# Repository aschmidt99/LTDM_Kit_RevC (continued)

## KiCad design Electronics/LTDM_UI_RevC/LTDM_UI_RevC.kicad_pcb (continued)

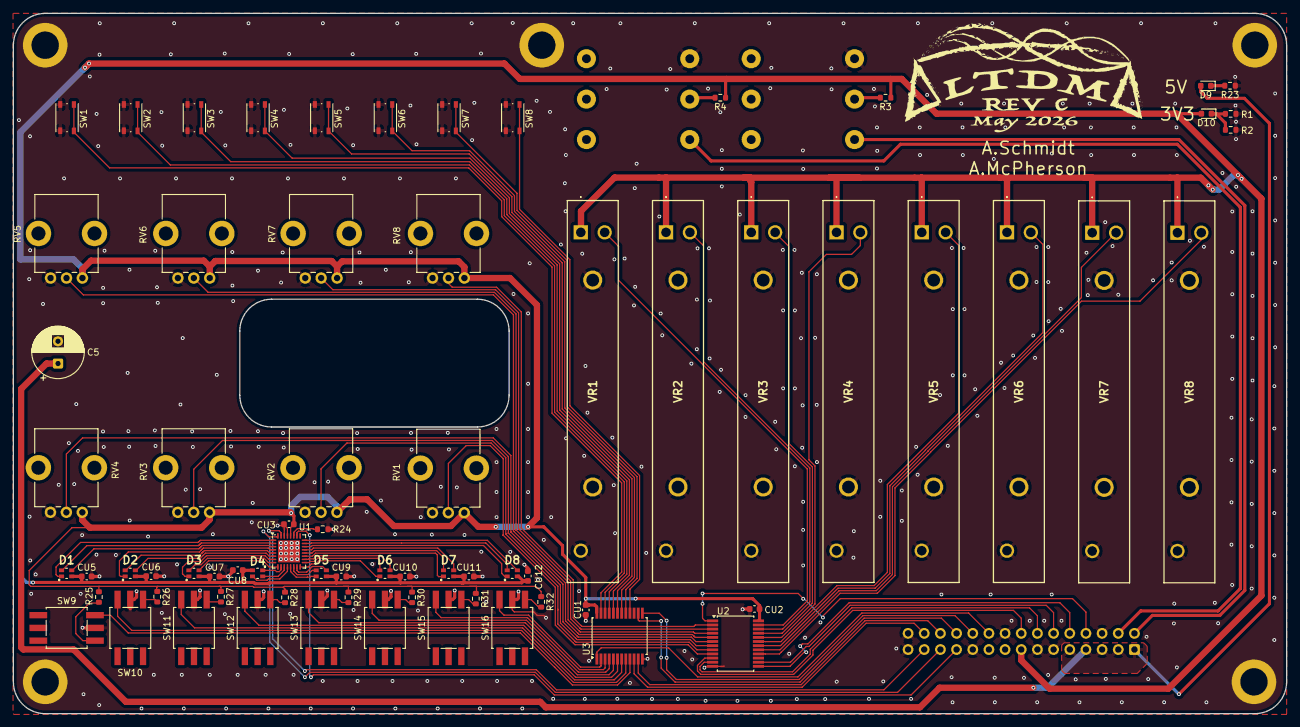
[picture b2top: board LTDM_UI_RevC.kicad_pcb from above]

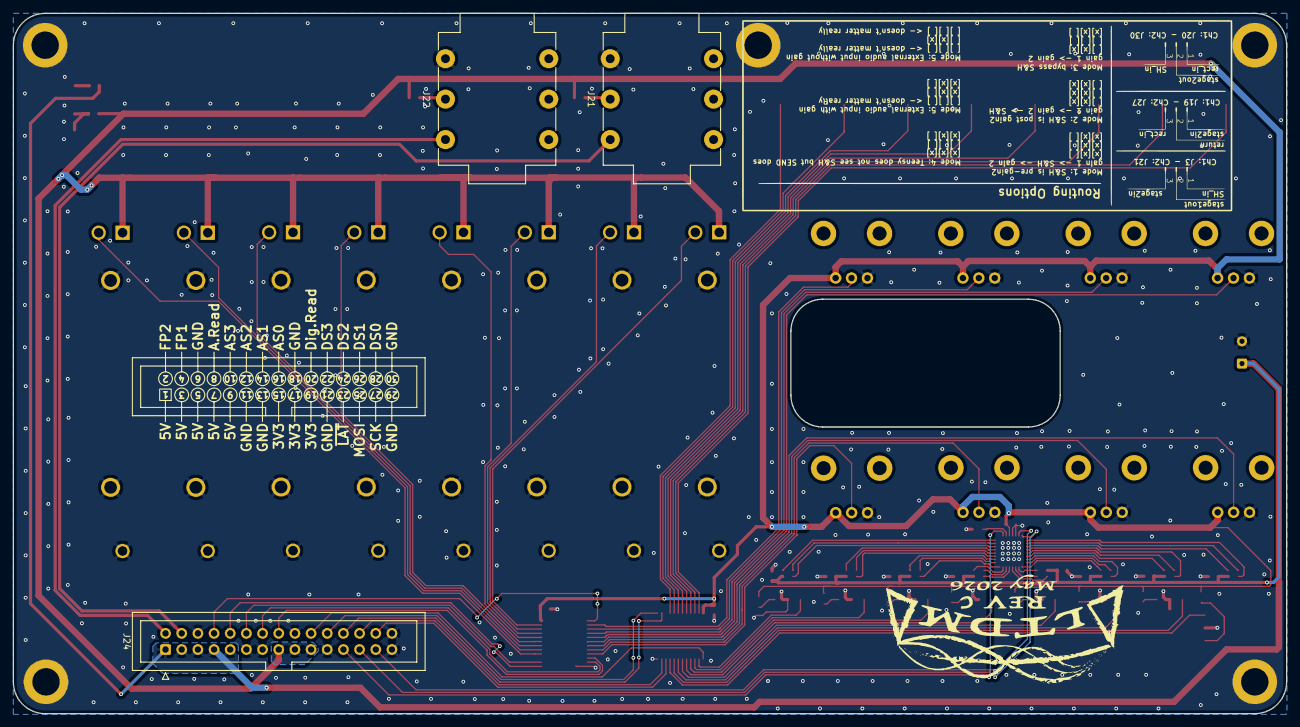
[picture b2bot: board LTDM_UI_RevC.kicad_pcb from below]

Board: 2 copper layers, 200.0 x 110.0 mm, 80 parts (4 on the bottom side), 87 nets.

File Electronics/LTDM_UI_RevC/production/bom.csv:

Designator,Footprint,Quantity,Value,LCSC Part #
C5,CP_Radial_D8.0mm_P3.50mm,1,220u,C45072
"CU1, CU10, CU11, CU12, CU2, CU3, CU5, CU6, CU7, CU8, CU9",0603,11,100n,
"D1, D2, D3, D4, D5, D6, D7, D8",19237R6GHBHCA012T,8,LED_RGBA,C60105
"D10, D9",0603,2,LED,C79636
"J21, J22",Jack_6.35mm_Neutrik_NMJ6HCD2_Horizontal,2,NMJ6HCD2,C368502
J24,IDC-Header_2x15_P2.54mm_Vertical,1,Conn_02x15_Odd_Even,C358748
"R1, R2, R23",0603,3,120,
R24,0603,1,2.2k,
"R25, R26, R27, R28, R29, R30, R31, R32",0603,8,10k,
"R3, R4",0603,2,100,
"RV1, RV2",Potentiometer_Bourns_PTV09A-1_Single_Vertical,2,10k, C5357831
"RV3, RV4, RV5, RV6, RV7, RV8",Potentiometer_Bourns_PTV09A-1_Single_Vertical,6,10k,C5357831
"SW1, SW2, SW3, SW4, SW5, SW6, SW7, SW8",SW_Push_1P1T_NO_Vertical_Wuerth_434133025816,8,tactile,C5504987
"SW10, SW11, SW12, SW13, SW14, SW15, SW16, SW9",SW_Push_DPDT_PS-5850SVB-6PL,8,SW_Push_DPDT,C5155567
U1,QFN-32-1EP_5x5mm_P0.5mm_EP3.45x3.45mm,1,TLC5947RHB,C181402
"U2, U3",SSOP-24_5.3x8.2mm_P0.65mm,2,CD74HC4067SM,C98457
"VR1, VR2, VR3, VR4, VR5, VR6, VR7, VR8",RS45111A900F,8,RS45111A900F,C470640

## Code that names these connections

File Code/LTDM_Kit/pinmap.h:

// pinmap.h
#ifndef PINMAP_H
#define PINMAP_H

// OUTPUTS //
// FLEX PWM definitions
constexpr int SENSE_ALT     = 4; // FlexPWM 2.0A - alternate sense pulse (in case of small timing adjustments for S&H)
constexpr int SENSE_PULSE   = 5; // FlexPWM 2.1A - primary sense pulse (triggers ISR, traditionally triggers S&H)
constexpr int CH1_PACTUATE  = 6; // FlexPWM 2.2A (Val2+3) - Channel 1 Actuate PMOS Positive Pulse
constexpr int CH1_NACTUATE  = 9; // FlexPWM 2.2B (Val4+5) - Channel 1 Actuate NMOS Negative Pulse
constexpr int CH2_PACTUATE  = 36; //FlexPWM 2.3A (Val2+3) - Channel 2 Actuate PMOS Positive Pulse
constexpr int CH2_NACTUATE  = 37; //FlexPWM 2.3B (Val4+5) - Channel 2 Actuate NMOS Negative Pulse
constexpr int MOTOR_ENN_SYNC = 33; // plain GPIO - momentary button 9 drives motor driver ENN sync line
constexpr int SYNC_PIN      = 1; // "GPIO1" header - FlexPWM 1.0_X out when SYNC_TX, XBAR1_INOUT16 in when SYNC_RX

constexpr int CH1_ENABLE    = 24; // must be high to permit Channel 1 to be on
constexpr int CH2_ENABLE    = 25; // must be high to permit Channel 2 to be on

constexpr int CH1_ADC_PIN       = 14; // (A0) for rectified analog input
constexpr int CH1_POLARITY_PIN  = 34; // for assessing polarity of signal (Postive or Negative)
constexpr int CH1_CURRSENSE_PIN = 27; // (A13) rectified current measurement input.

constexpr int CH2_ADC_PIN       = 15; // (A1?) for rectified analog input
constexpr int CH2_POLARITY_PIN  = 35; // for assessing polarity of signal (Postive or Negative)
constexpr int CH2_CURRSENSE_PIN = 26; // (A12) rectified current measurement input

constexpr int TEMP_FAULT_RESET = 7; // plain GPIO, grounded/floating by default - driven HIGH while button 10 is held
constexpr int SERVO_PIN = 28; // pin for attaching servo

// INPUTS //
// UI multiplexers for buttons, sliders, and pots
// Buttons
constexpr int DSIN  = 2;
constexpr int DS0   = 32;
constexpr int DS1   = 31;
constexpr int DS2   = 30;
constexpr int DS3   = 3;

// Sliders & Pots
constexpr int ASIN  = 16;
constexpr int AS0   = 38;
constexpr int AS1   = 39;
constexpr int AS2   = 40;
constexpr int AS3   = 41;

// Footpedal inputs
constexpr int FP0  = 22;
constexpr int FP1  = 23;

// TLC5947 LED Driver
constexpr int tlc_data   = 11;
constexpr int tlc_clock  = 13;
constexpr int tlc_latch  = 8;

#endif // PINMAP_H

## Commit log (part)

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2026-03-24 Improved and characterized ADC sample time
    Previously took ~6.3uS to sample both ADCs but have gotten it down to a sweet ~3.4uS by disabling 'long sampling mode' and ADC_CFG_ADSTS(3) to ADC_CFG_ADSTS(0). Apparently that was upping sample time.
    This arrangement is likely noisier but gives a user an extra 3.5uS to play with in render()
    This is for 600MHz.
    Trimming away old code too :)
2026-03-25 Reinstated RMS + noise (and now a rudimentary lowpass on noise!)
    This is the code brought to the Marco Fusi session!
    RMS limiting now actually actively damps when the RMS is measured too high. Neat!
2026-04-13 Channel 2 fixed!
    Channel 2 now working again
    Now you can enable/disable RMS limiting and noise
    LEDs indicate settings (refer to visualguide.jpg)
2026-04-13 fix .jpg
2026-05-18 Boards Ordered!
    The KiCad files are the ones that were ordered
2026-06-21 About to start messing with Serial connectivity to max/msp
2026-06-21 sped up the ISR and the process function
2026-06-23 Reinstated Serial Communication via Max. Updated Max Patch.
    Max Patch can now override hardware UI if desired.
2026-06-23 Update comments
    Update comments for clarity in render.cpp. Remove some outdated comments from main .ino file.
